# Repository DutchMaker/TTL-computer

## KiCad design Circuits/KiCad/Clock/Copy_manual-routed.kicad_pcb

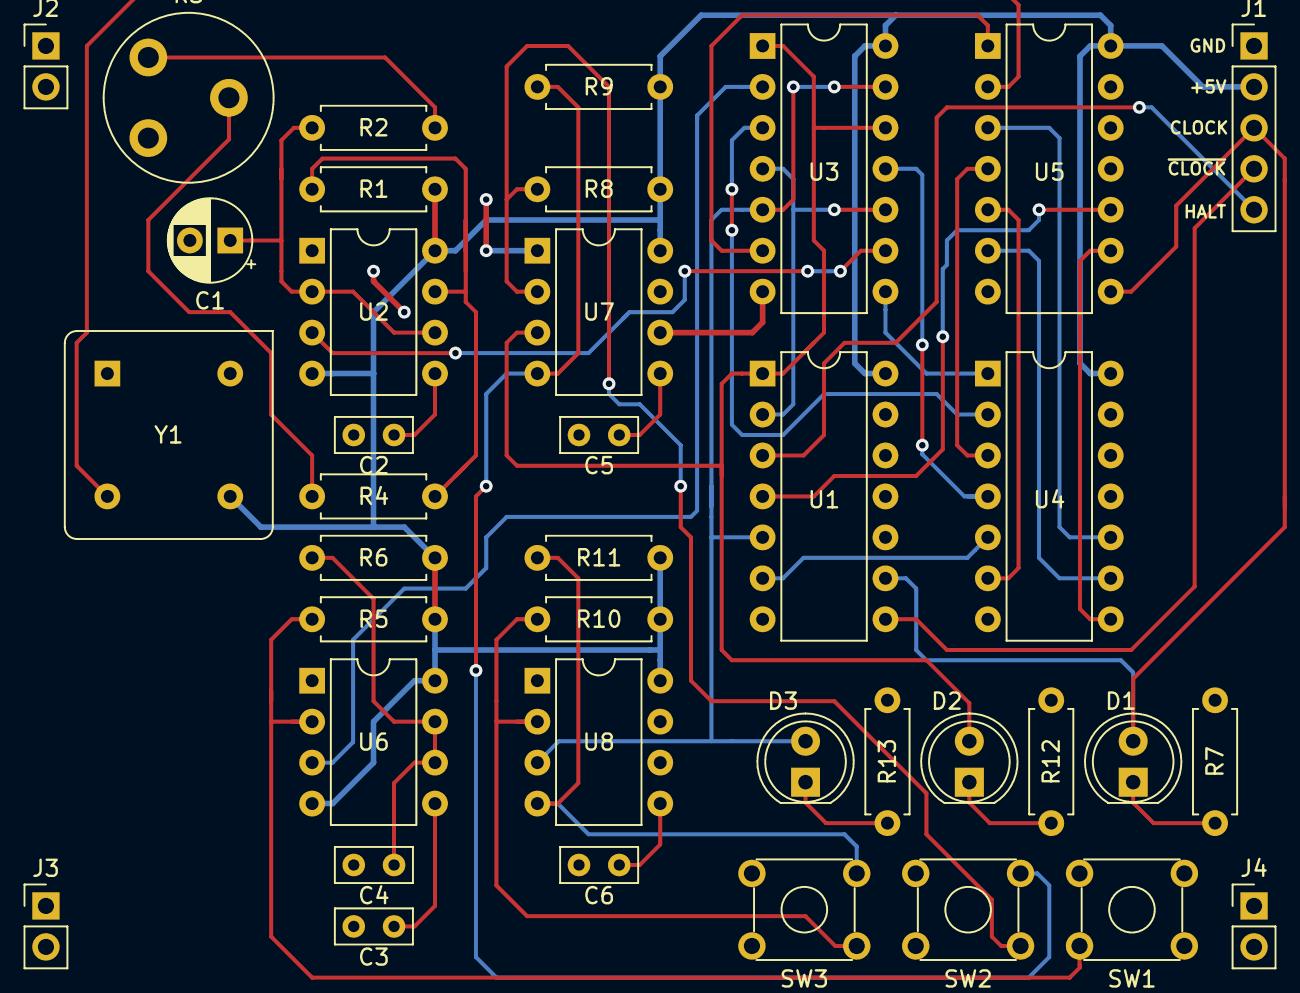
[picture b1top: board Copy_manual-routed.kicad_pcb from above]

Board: 2 copper layers, 38 parts (0 on the bottom side), 39 nets.

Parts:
C1: 1uF; CP_Radial_D5.0mm_P2.50mm
C2, C3, C5, C6: 10nF; C_Rect_L4.6mm_W2.0mm_P2.50mm_MKS02_FKP02
C4: 100nF; C_Rect_L4.6mm_W2.0mm_P2.50mm_MKS02_FKP02
D1, D2, D3: LED; LED_D5.0mm
J1: Conn_01x05_Male; PinHeader_1x05_P2.54mm_Vertical
J2, J3, J4: Conn_01x02_Male; PinHeader_1x02_P2.54mm_Vertical
R1, R4, R5, R8, R9, R10, R11: 1K; R_Axial_DIN0207_L6.3mm_D2.5mm_P7.62mm_Horizontal
R2: 47K; R_Axial_DIN0207_L6.3mm_D2.5mm_P7.62mm_Horizontal
R3: 1M; Potentiometer_Piher_PT-10-V05_Vertical
R6: 1M; R_Axial_DIN0207_L6.3mm_D2.5mm_P7.62mm_Horizontal
R7, R12, R13: 330; R_Axial_DIN0207_L6.3mm_D2.5mm_P7.62mm_Horizontal
SW1: SW_Push; SW_TH_Tactile_Omron_B3F-10xx
SW2, SW3: SW_Push_SPDT; SW_TH_Tactile_Omron_B3F-10xx
U1: 74x04; DIP-14_W7.62mm
U2, U6, U7, U8: 555; DIP-8_W7.62mm
U3, U5: 74x08; DIP-14_W7.62mm
U4: 74x32; DIP-14_W7.62mm
Y1: 1 MHz; Oscillator_DIP-8_v2

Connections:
+5V: J1.2, R1.2, R5.2, R6.1, R8.2, R9.2, R10.2, R11.2, U1.14, U2.4, U2.8, U3.14, U4.14, U5.14, U6.4, U6.8, U7.8, U8.8, Y1.1
CLK_HLT: J1.5, U1.3
CLK_MAN: U3.2, U6.3
CLK_MAN_EN: D2.2, U1.1, U3.1, U3.12, U7.3
CLK_TURBO: U5.2, Y1.3
CLK_TURBO_EN: D3.2, U1.5, U3.5, U3.13, U8.3
CLK_VAR: U2.3, U3.9
CLOCK: D1.2, J1.3, U1.9, U5.8
GND: C1.2, C2.2, C3.2, C4.2, C5.2, C6.2, J1.1, R7.2, R12.2, R13.2, SW1.1, SW2.2, SW3.2, U1.7, U2.1, U3.7, U4.7, U5.7, U6.1, U7.1, U7.6, U8.1, U8.6, Y1.2
unnamed: C1.1, R2.1, U2.2, U2.6
unnamed: C2.1, U2.5
unnamed: C3.1, U6.5
unnamed: C4.1, R6.2, U6.6, U6.7
unnamed: C5.1, U7.5
unnamed: C6.1, U8.5
unnamed: D1.1, R7.1
unnamed: D2.1, R12.1
unnamed: D3.1, R13.1
unnamed: R1.1, R4.1, U2.7
unnamed: R2.2, R3.3
unnamed: R3.2, R4.2
unnamed: R5.1, SW1.2, U6.2
unnamed: R8.1, SW2.1, U7.2
unnamed: R9.1, SW2.3, U7.4
unnamed: R10.1, SW3.1, U8.2
unnamed: R11.1, SW3.3, U8.4
unnamed: U1.2, U3.4, U3.10
unnamed: U1.4, U5.10
unnamed: U1.6, U4.5
unnamed: U3.3, U4.2
unnamed: U3.6, U5.1
unnamed: U3.8, U4.1
unnamed: U3.11, U4.4
unnamed: U4.3, U5.4
unnamed: U4.6, U5.5
unnamed: U4.8, U5.9
unnamed: U4.9, U5.6
unnamed: U4.10, U5.3
~CLOCK: J1.4, U1.8

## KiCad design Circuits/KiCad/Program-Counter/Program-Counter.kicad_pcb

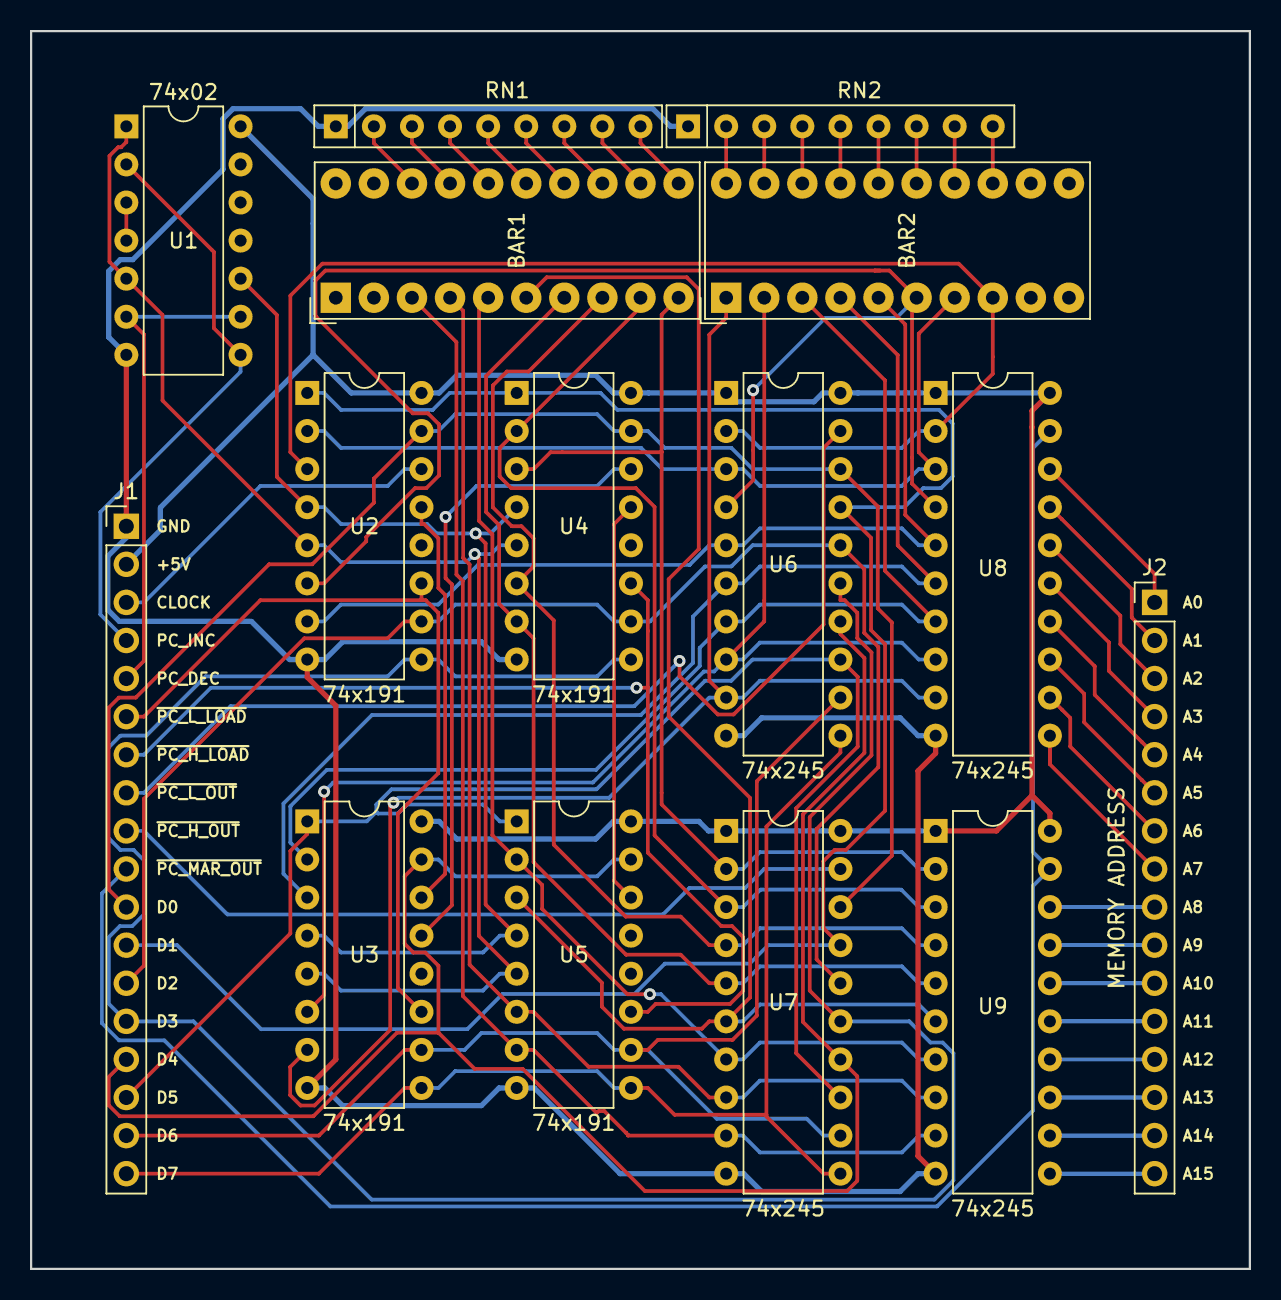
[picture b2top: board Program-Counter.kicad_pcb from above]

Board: 2 copper layers, 81.3 x 82.5 mm, 15 parts (0 on the bottom side), 72 nets.

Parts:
BAR1, BAR2: HDSP-4830_2; HDSP-4830
J1: Conn_01x18_Male; PinHeader_1x18_P2.54mm_Vertical
J2: MEMORY ADDRESS; PinHeader_1x16_P2.54mm_Vertical
RN1, RN2: 470; R_Array_SIP9
U1: 74x02; DIP-14_W7.62mm
U2, U3, U4, U5: 74x191; DIP-16_W7.62mm
U6, U7, U8, U9: 74x245; DIP-20_W7.62mm

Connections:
+5V: J1.2, U1.14, U2.16, U3.16, U4.16, U5.16, U6.1, U6.20, U7.1, U7.20, U8.1, U8.20, U9.1, U9.20
CLOCK: J1.3, U2.14
DATA_BUS0: J1.11, U2.15, U4.15, U6.18, U7.18
DATA_BUS1: J1.12, U2.1, U4.1, U6.17, U7.17
DATA_BUS2: J1.13, U2.10, U4.10, U6.16, U7.16
DATA_BUS3: J1.14, U2.9, U4.9, U6.15, U7.15
DATA_BUS4: J1.15, U3.15, U5.15, U6.14, U7.14
DATA_BUS5: J1.16, U3.1, U5.1, U6.13, U7.13
DATA_BUS6: J1.17, U3.10, U5.10, U6.12, U7.12
DATA_BUS7: J1.18, U3.9, U5.9, U6.11, U7.11
DOWN_~UP: U1.1, U1.5, U2.5, U3.5, U4.5, U5.5
GND: J1.1, RN1.1, RN2.1, U1.7, U2.8, U3.8, U4.8, U5.8, U6.10, U7.10, U8.10, U9.10
unnamed: BAR1.3, U5.7, U7.9, U9.9
unnamed: BAR1.4, U5.6, U7.8, U9.8
unnamed: BAR1.5, U5.2, U7.7, U9.7
unnamed: BAR1.6, U5.3, U7.6, U9.6
unnamed: BAR1.7, U4.7, U7.5, U9.5
unnamed: BAR1.8, U4.6, U7.4, U9.4
unnamed: BAR1.9, U4.2, U7.3, U9.3
unnamed: BAR1.10, U4.3, U7.2, U9.2
unnamed: BAR1.11, RN1.9
unnamed: BAR1.12, RN1.8
unnamed: BAR1.13, RN1.7
unnamed: BAR1.14, RN1.6
unnamed: BAR1.15, RN1.5
unnamed: BAR1.16, RN1.4
unnamed: BAR1.17, RN1.3
unnamed: BAR1.18, RN1.2
unnamed: BAR2.1, U3.7, U6.9, U8.9
unnamed: BAR2.2, U3.6, U6.8, U8.8
unnamed: BAR2.3, U3.2, U6.7, U8.7
unnamed: BAR2.4, U3.3, U6.6, U8.6
unnamed: BAR2.5, U2.7, U6.5, U8.5
unnamed: BAR2.6, U2.6, U6.4, U8.4
unnamed: BAR2.7, U2.2, U6.3, U8.3
unnamed: BAR2.8, U2.3, U6.2, U8.2
unnamed: BAR2.13, RN2.9
unnamed: BAR2.14, RN2.8
unnamed: BAR2.15, RN2.7
unnamed: BAR2.16, RN2.6
unnamed: BAR2.17, RN2.5
unnamed: BAR2.18, RN2.4
unnamed: BAR2.19, RN2.3
unnamed: BAR2.20, RN2.2
unnamed: J2.1, U8.18
unnamed: J2.2, U8.17
unnamed: J2.3, U8.16
unnamed: J2.4, U8.15
unnamed: J2.5, U8.14
unnamed: J2.6, U8.13
unnamed: J2.7, U8.12
unnamed: J2.8, U8.11
unnamed: J2.9, U9.18
unnamed: J2.10, U9.17
unnamed: J2.11, U9.16
unnamed: J2.12, U9.15
unnamed: J2.13, U9.14
unnamed: J2.14, U9.13
unnamed: J2.15, U9.12
unnamed: J2.16, U9.11
unnamed: U1.3, U1.4
unnamed: U2.13, U3.14
unnamed: U3.13, U4.14
unnamed: U4.13, U5.14
PC_DEC: J1.5, U1.6, U1.9
PC_INC: J1.4, U1.2, U1.8
~CLK_EN: U1.10, U2.4, U3.4, U4.4, U5.4
~PC_H_LOAD: J1.7, U4.11, U5.11
~PC_H_OUT: J1.9, U7.19
~PC_L_LOAD: J1.6, U2.11, U3.11
~PC_L_OUT: J1.8, U6.19
~PC_MAR_OUT: J1.10, U8.19, U9.19

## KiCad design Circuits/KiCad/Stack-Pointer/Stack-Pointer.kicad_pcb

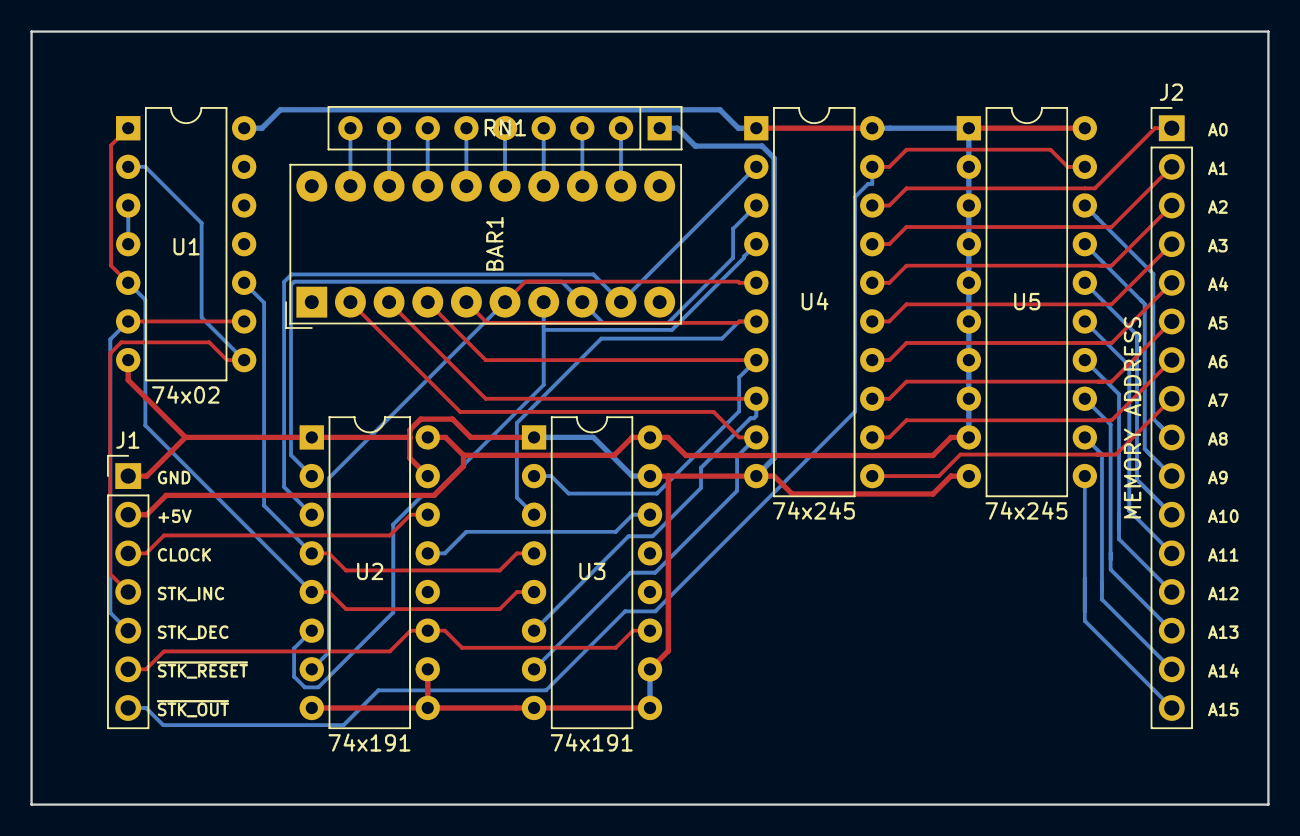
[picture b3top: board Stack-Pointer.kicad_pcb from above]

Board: 2 copper layers, 81.3 x 50.8 mm, 9 parts (0 on the bottom side), 43 nets.

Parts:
BAR1: HDSP-4830_2; HDSP-4830
J1: Conn_01x07_Male; PinHeader_1x07_P2.54mm_Vertical
J2: MEMORY ADDRESS; PinHeader_1x16_P2.54mm_Vertical
RN1: 470; R_Array_SIP9
U1: 74x02; DIP-14_W7.62mm
U2, U3: 74x191; DIP-16_W7.62mm
U4, U5: 74x245; DIP-20_W7.62mm

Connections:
+5V: J1.2, U1.14, U2.16, U3.16, U4.1, U4.20, U5.1, U5.2, U5.3, U5.4, U5.5, U5.6, U5.7, U5.8, U5.9, U5.20
CLOCK: J1.3, U2.14
DOWN_~UP: U1.1, U1.5, U2.5, U3.5
GND: J1.1, RN1.1, U1.7, U2.1, U2.8, U2.9, U2.10, U2.15, U3.1, U3.8, U3.9, U3.10, U3.15, U4.10, U5.10
unnamed: BAR1.2, U3.7, U4.9
unnamed: BAR1.3, U3.6, U4.8
unnamed: BAR1.4, U3.2, U4.7
unnamed: BAR1.5, U3.3, U4.6
unnamed: BAR1.6, U2.7, U4.5
unnamed: BAR1.7, U2.6, U4.4
unnamed: BAR1.8, U2.2, U4.3
unnamed: BAR1.9, U2.3, U4.2
unnamed: BAR1.12, RN1.2
unnamed: BAR1.13, RN1.3
unnamed: BAR1.14, RN1.4
unnamed: BAR1.15, RN1.5
unnamed: BAR1.16, RN1.6
unnamed: BAR1.17, RN1.7
unnamed: BAR1.18, RN1.8
unnamed: BAR1.19, RN1.9
unnamed: J2.1, U4.18
unnamed: J2.2, U4.17
unnamed: J2.3, U4.16
unnamed: J2.4, U4.15
unnamed: J2.5, U4.14
unnamed: J2.6, U4.13
unnamed: J2.7, U4.12
unnamed: J2.8, U4.11
unnamed: J2.9, U5.18
unnamed: J2.10, U5.17
unnamed: J2.11, U5.16
unnamed: J2.12, U5.15
unnamed: J2.13, U5.14
unnamed: J2.14, U5.13
unnamed: J2.15, U5.12
unnamed: J2.16, U5.11
unnamed: U1.3, U1.4
unnamed: U2.13, U3.14
STK_DEC: J1.5, U1.6, U1.9
STK_INC: J1.4, U1.2, U1.8
~CLK_EN: U1.10, U2.4, U3.4
~STK_OUT: J1.7, U4.19, U5.19
~STK_RESET: J1.6, U2.11, U3.11
